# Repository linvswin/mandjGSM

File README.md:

#### Working in progress !!!
# mandjGSM
## Cosa &egrave;? 
modulo GSM per la centralina mandjBeep V2

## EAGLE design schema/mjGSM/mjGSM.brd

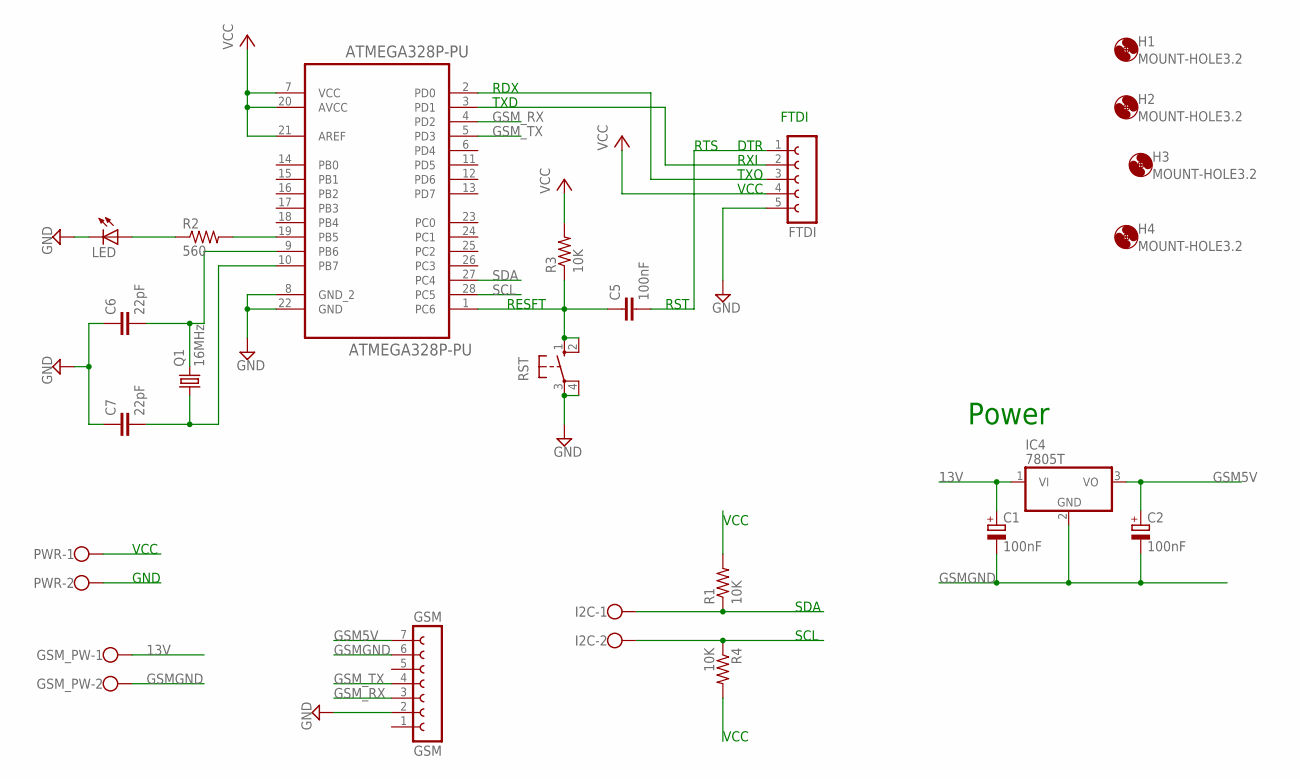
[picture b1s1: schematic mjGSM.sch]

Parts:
ATMEGA328P-PU: ATMEGA328P-PU; DIP254P762X457-28
C1, C2: 100nF; E2-4
C5: 100nF; C025-024X044
C6, C7: 22pF; C025-024X044
FTDI: FE05-1
GSM: GSM; FE07
GSM_PW: W237-102
H1, H2, H3, H4: MOUNT-HOLE3.2; 3,2
I2C: W237-102
IC4: 7805T; TO220H
LED: LED3MM
PWR: W237-102
Q1: 16MHz; HC49/S
R1, R3, R4: 10K; 0204/5
R2: 560; 0204/5
RST: 10-XX; B3F-10XX

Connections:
13V: C1.+, GSM_PW.1, IC4.1 (VI)
GND: ATMEGA328P-PU.8 (GND_2), ATMEGA328P-PU.22 (GND), C6.1, C7.1, FTDI.5, GSM.2, LED.K (C), PWR.2, RST.3, RST.4 (P1)
GSM5V: C2.+, GSM.7, IC4.3 (VO)
GSMGND: C1.-, C2.-, GSM.6, GSM_PW.2, IC4.2 (GND)
GSM_RX: ATMEGA328P-PU.4 (PD2), GSM.3
GSM_TX: ATMEGA328P-PU.5 (PD3), GSM.4
unnamed: LED.A, R2.1
unnamed: ATMEGA328P-PU.19 (PB5), R2.2
unnamed: ATMEGA328P-PU.2 (PD0), FTDI.3
unnamed: ATMEGA328P-PU.3 (PD1), FTDI.2
unnamed: ATMEGA328P-PU.1 (PC6), C5.1, R3.1, RST.1 (S), RST.2 (S1)
unnamed: ATMEGA328P-PU.9 (PB6), C6.2, Q1.2
unnamed: C5.2, FTDI.1
unnamed: ATMEGA328P-PU.10 (PB7), C7.2, Q1.1
SCL: ATMEGA328P-PU.28 (PC5), I2C.2, R4.1
SDA: ATMEGA328P-PU.27 (PC4), I2C.1, R1.1
VCC: ATMEGA328P-PU.7 (VCC), ATMEGA328P-PU.20 (AVCC), ATMEGA328P-PU.21 (AREF), FTDI.4, PWR.1, R1.2, R3.2, R4.2

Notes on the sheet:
RDX
TXD
RST
RESFT
RTS
SDA
SCL
VCC
GND
DTR
RXI
TXO
FTDI
Power

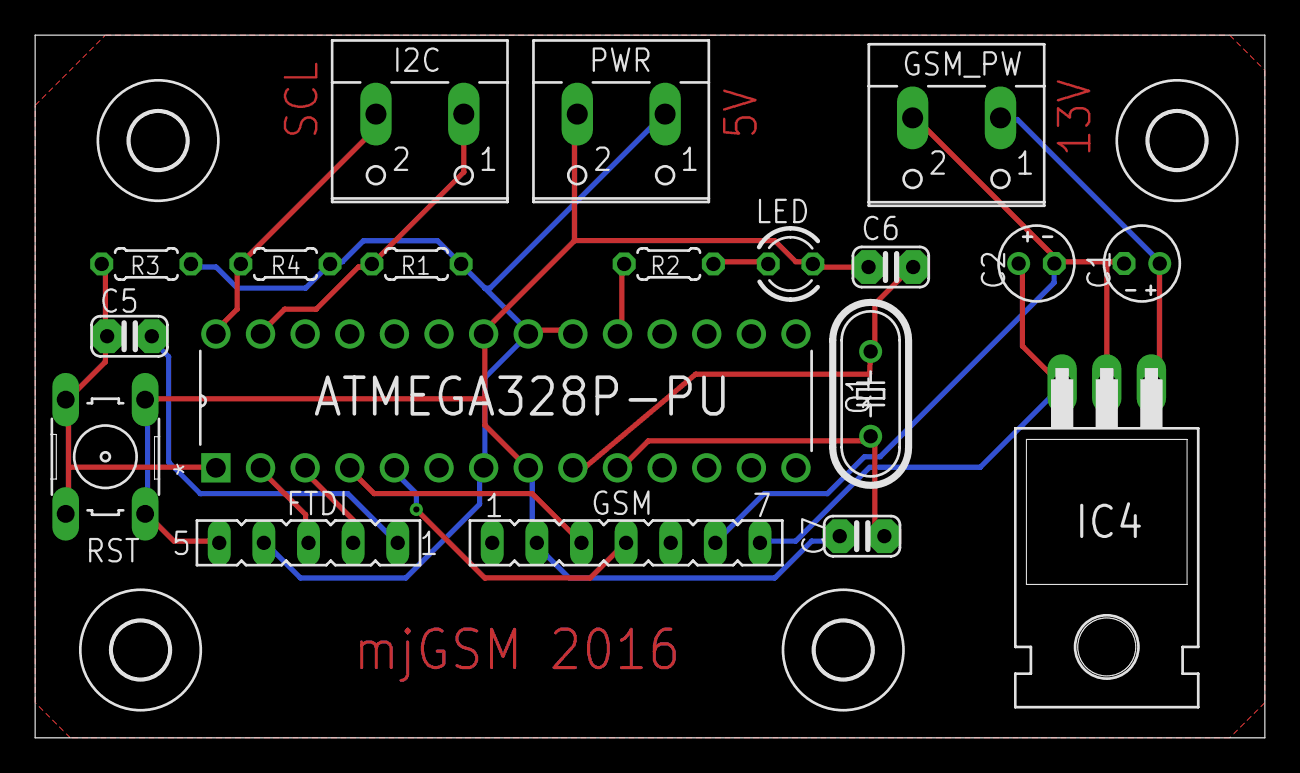
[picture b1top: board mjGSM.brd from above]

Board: 2 copper layers, 70.0 x 40.0 mm, 23 parts (0 on the bottom side), 17 nets.
